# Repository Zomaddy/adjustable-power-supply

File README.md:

adjustable +/- 15V power supply

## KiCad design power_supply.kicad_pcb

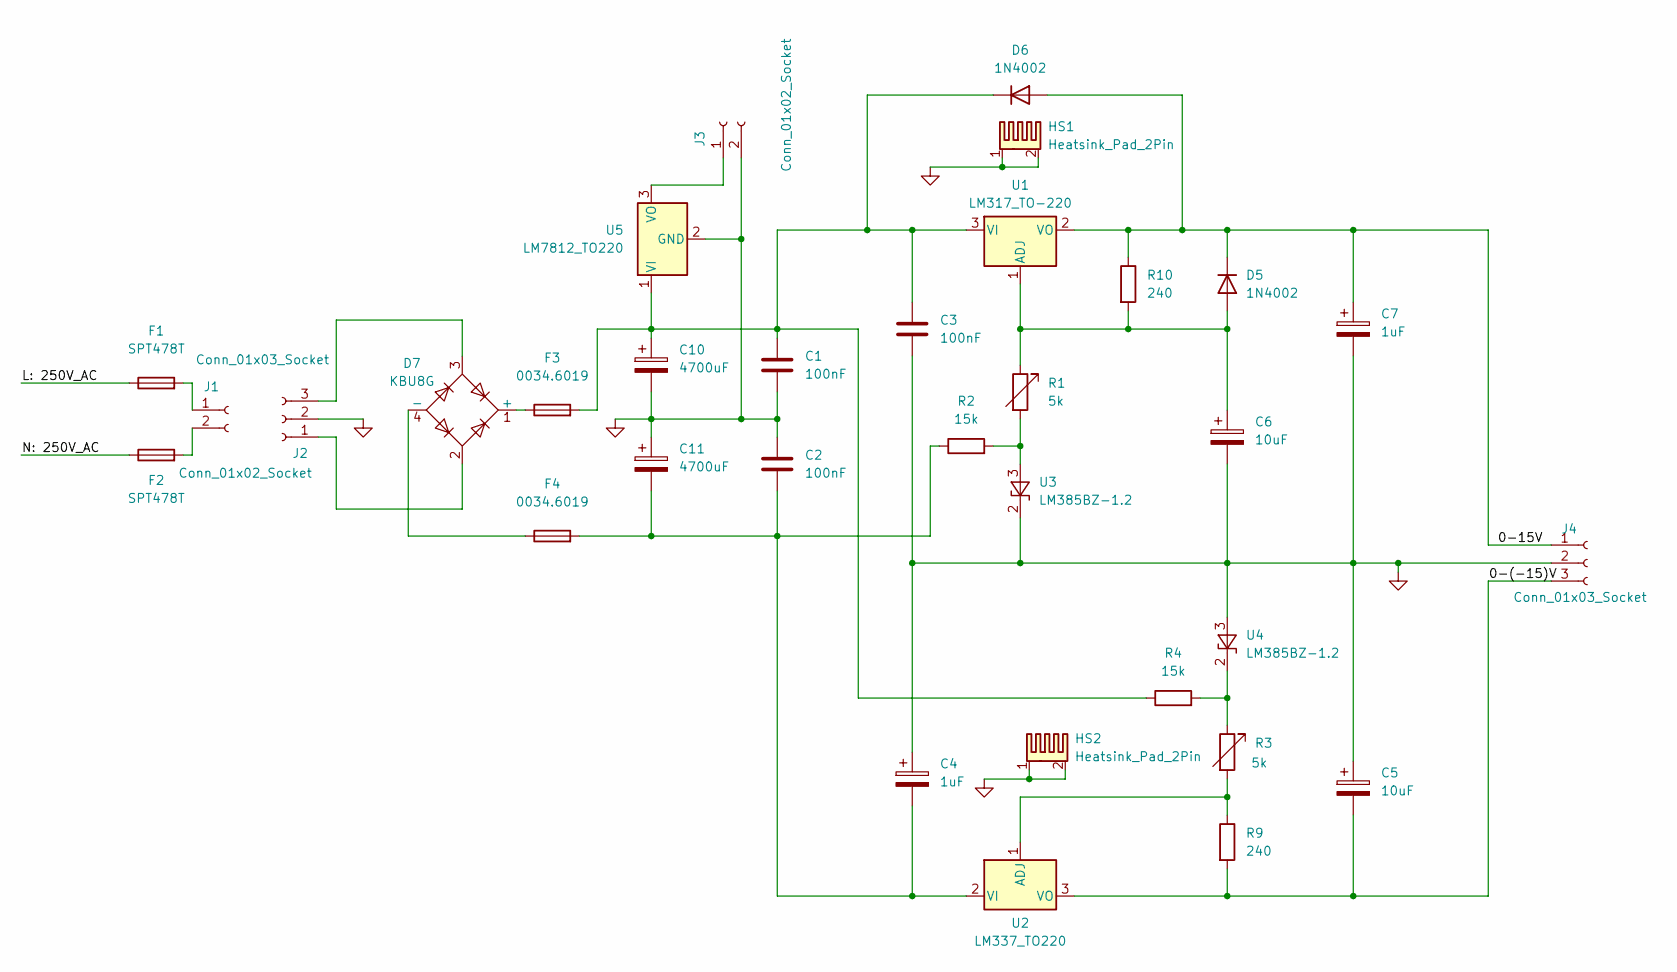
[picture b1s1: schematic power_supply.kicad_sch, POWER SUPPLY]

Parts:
C1, C2, C3: 100nF; C_Rect_L7.5mm_W6.5mm_P5.00mm
C4, C7: 1uF; CP_Radial_D5.0mm_P2.00mm
C5, C6: 10uF; CP_Radial_D5.0mm_P2.00mm
C10, C11: 4700uF; CP_Radial_D16.0mm_P7.50mm
D5, D6: 1N4002; D_DO-41_SOD81_P10.16mm_Horizontal
D7: KBU8G; Diode_Bridge_Vishay_KBU
F1, F2: SPT478T
F3, F4: 0034.6019
HS1, HS2: Heatsink_Pad_2Pin; RAT2X51E
J1, J3: Conn_01x02_Socket; PhoenixContact_MSTBA_2,5_2-G_1x02_P5.00mm_Horizontal
J2, J4: Conn_01x03_Socket; PhoenixContact_MSTBA_2,5_3-G_1x03_P5.00mm_Horizontal
R1, R3: 5k; Potentiometer_Omeg_PC16BU_Vertical
R2, R4: 15k; R_Axial_DIN0207_L6.3mm_D2.5mm_P10.16mm_Horizontal
R9, R10: 240; R_Axial_DIN0207_L6.3mm_D2.5mm_P10.16mm_Horizontal
U1: LM317_TO-220; TO-220-3_Vertical
U2: LM337_TO220; TO-220-3_Vertical
U3, U4: LM385BZ-1.2; TO-92_Inline
U5: LM7812_TO220; TO-220-3_Vertical

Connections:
/0-15V: C7.1, D5.1 (K), D6.2 (A), J4.1, R10.1, U1.2 (VO)
/0-(-15)V: C5.2, J4.3, R9.2, U2.3 (VO)
GND: C1.2, C2.1, C3.2, C4.1, C5.1, C6.2, C7.2, C10.2, C11.1, HS1.1, HS1.2, HS2.1, HS2.2, J2.2, J3.2, J4.2, U3.2 (K), U4.3 (A), U5.2 (GND)
unnamed: C6.1, D5.2 (A), R1.1, R10.2, U1.1 (ADJ)
unnamed: C1.1, C3.1, C10.1, D6.1 (K), F3.2, R4.1, U1.3 (VI), U5.1 (VI)
unnamed: D7.1 (+), F3.1
unnamed: D7.4 (-), F4.1
unnamed: F1.2, J1.1
unnamed: F2.2, J1.2
unnamed: D7.2, J2.1
unnamed: D7.3, J2.3
unnamed: J3.1, U5.3 (VO)
unnamed: R3.2, R9.1, U2.1 (ADJ)
unnamed: C2.2, C4.2, C11.2, F4.2, R2.1, U2.2 (VI)
unnamed: R1.2, R2.2, U3.3 (A)
unnamed: R3.1, R4.2, U4.2 (K)

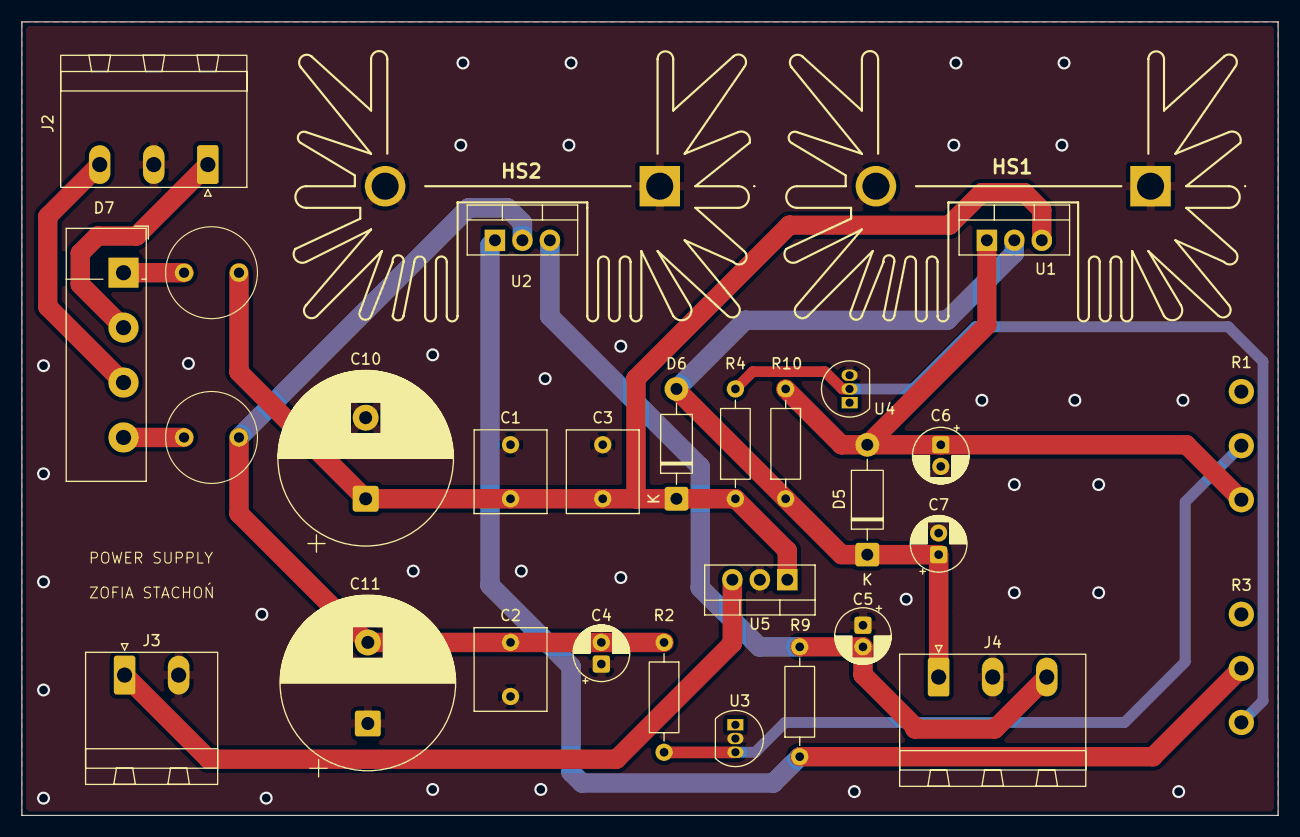
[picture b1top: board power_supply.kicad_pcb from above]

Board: 2 copper layers, 116.2 x 73.4 mm, 30 parts (0 on the bottom side), 14 nets.
